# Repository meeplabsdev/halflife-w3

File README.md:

# Piano Keys

# What it is
For the third week of [halflife](https://halflife.hackclub.com/), I decided to create a midi instrument. It uses capacitive touch to recognise when the keys are pressed, and use 16 zones per key (multiplexed). This means that while each key is single touch itself, it supports full multi touch across all the keys. It also allows us to determine the exact position of the finger on the key by taking readings from each zone and interpolating between them (since the readings differ depending on how close or far you are from each zone). It ALSO allows us to determine the velocity the key was pressed with and also the aftertouch pressure being applied, which can be approximated by the rate of change of the distance proxy, and by the reading produced by each zone respectively. (If four zones, one on each size of the finger, all show a lower reading then the finger is not compressed against the key, and if they show a higher reading it is because the finger is pushed harder against the key and has spread out).

# Schematic

# PCB (4 layers)

# Cost
This is a rough outline of the cost, see [`BOM.csv`](BOM.csv) for more details.

| Part | Cost |
| --- | --- |
| [Unpopulated PCB](https://jlcpcb.com/) | $62.10 |
| [Pi Pico](https://thepihut.com/products/raspberry-pi-pico?variant=41925332533443) | $5.08 |
| [Multiplexers](https://www.lcsc.com/product-detail/C6525.html) | $15.11 |
| **Total + Shipping** | **$99.56** |

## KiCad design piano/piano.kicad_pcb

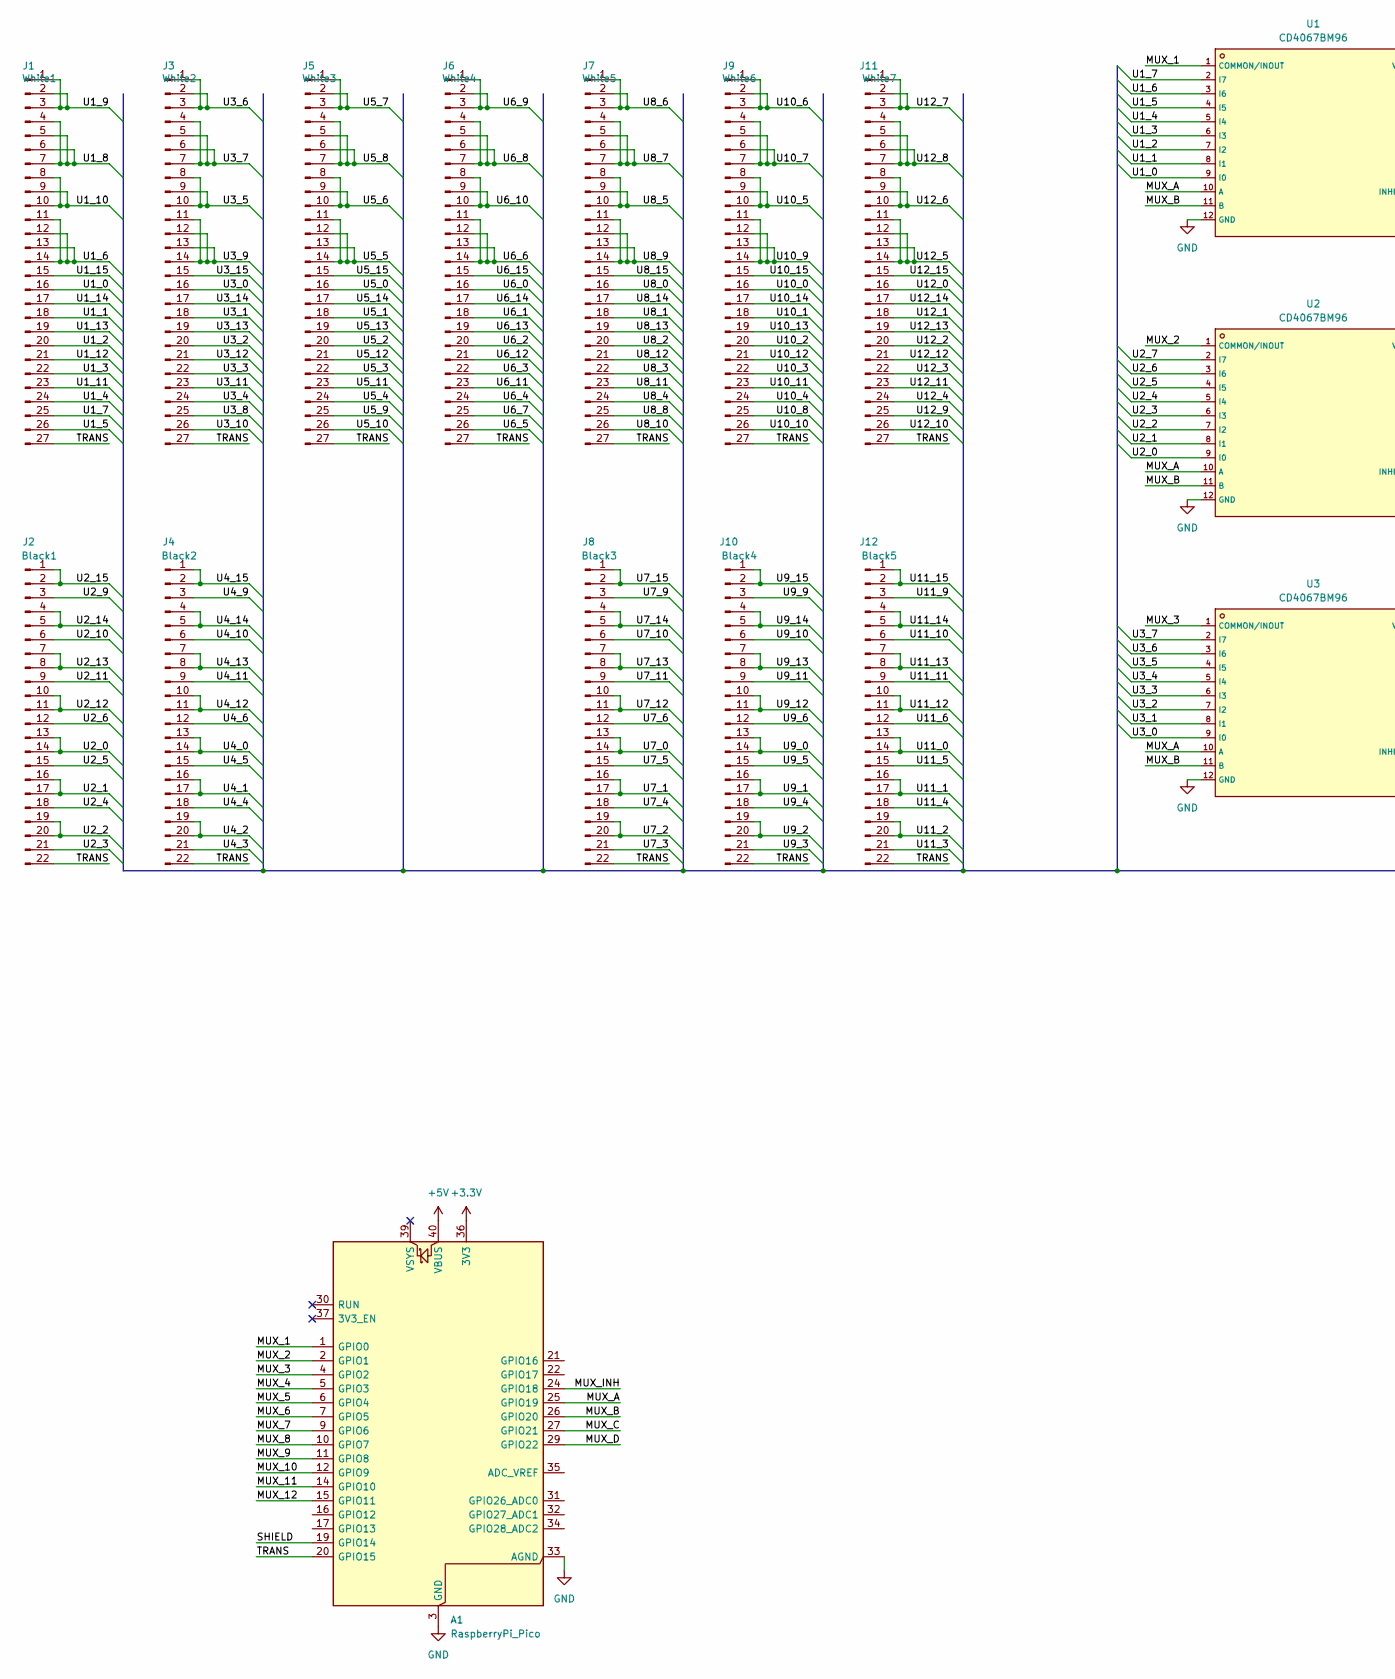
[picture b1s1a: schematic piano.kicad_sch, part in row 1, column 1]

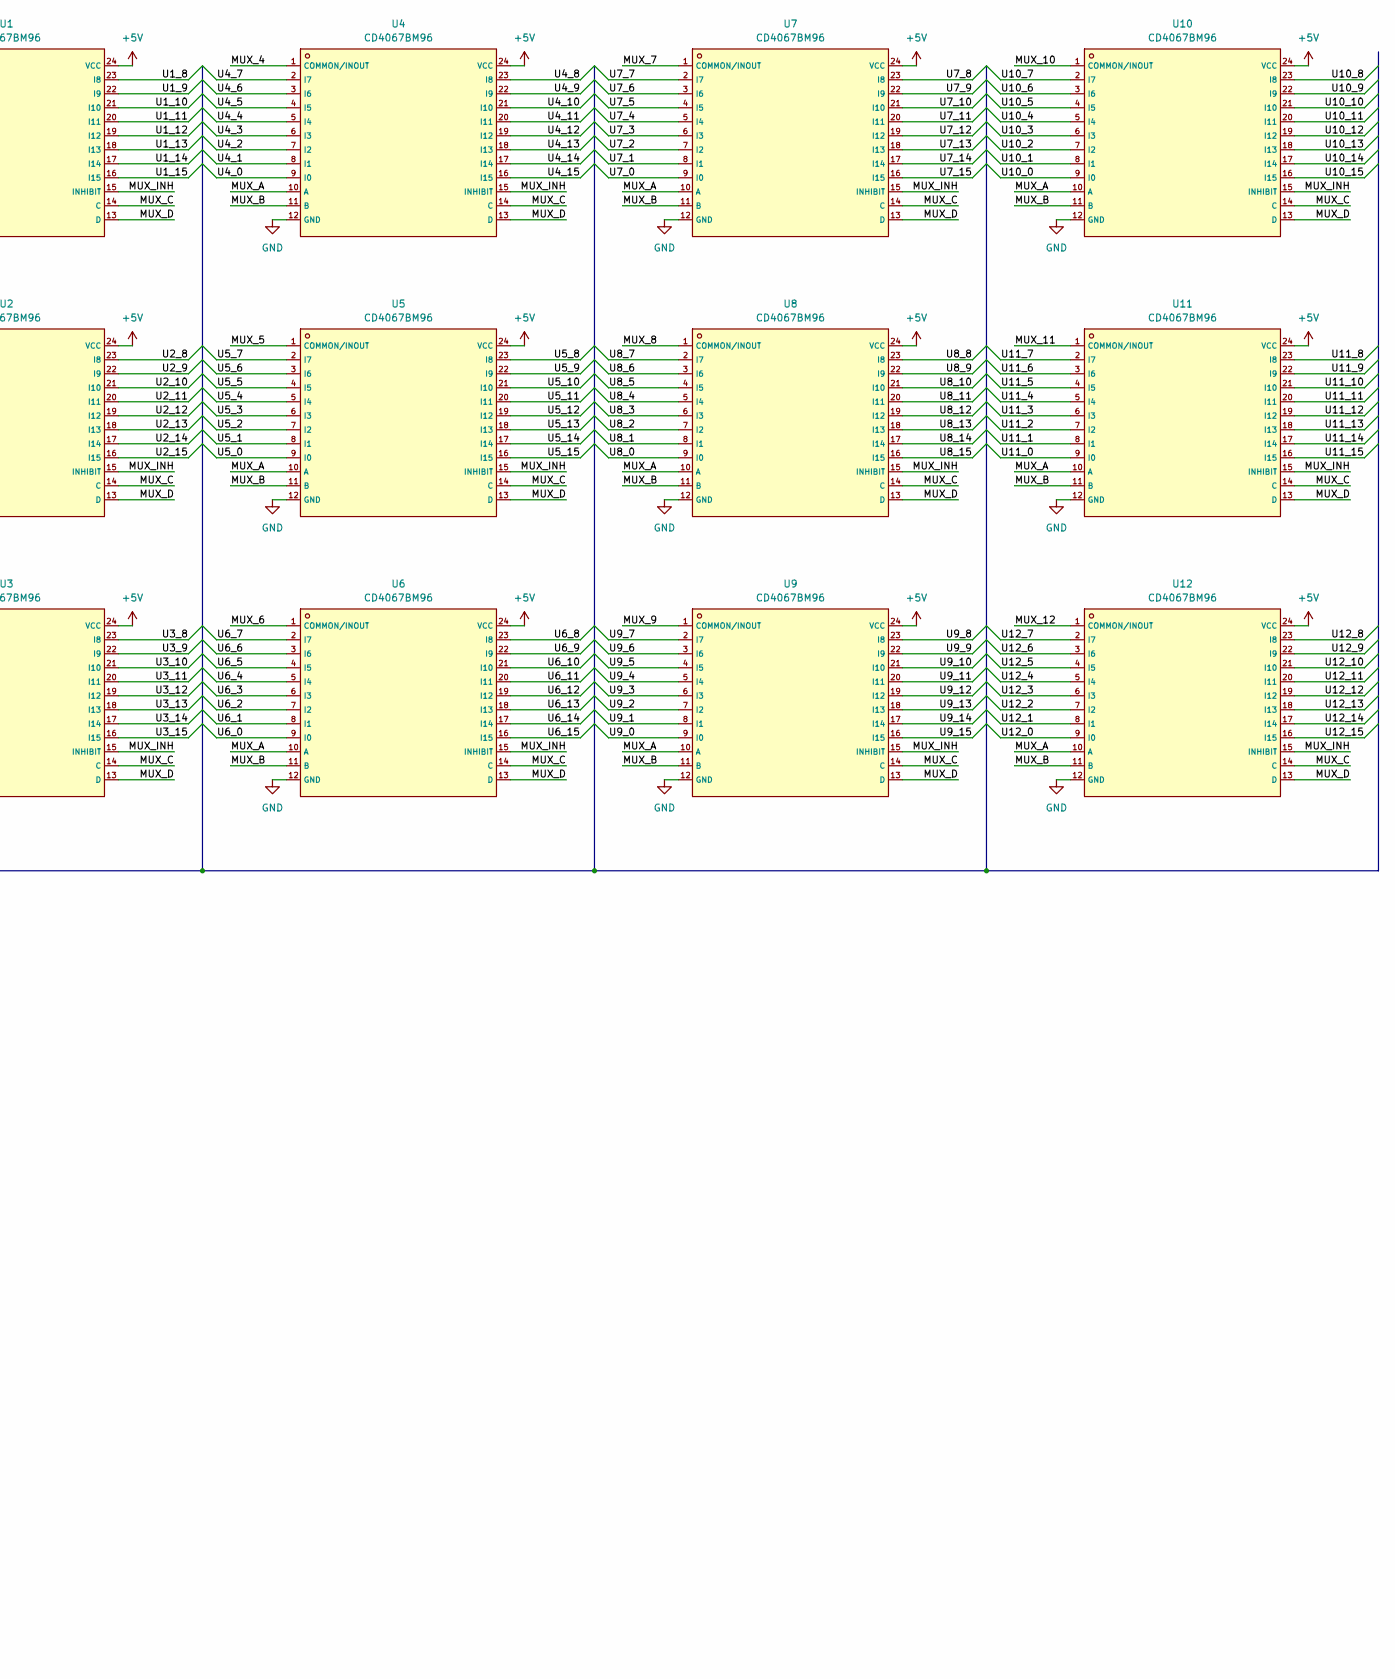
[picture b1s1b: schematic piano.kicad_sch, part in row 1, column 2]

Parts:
A1: RaspberryPi_Pico; RaspberryPi_Pico_Common_SMD
J1: White1; LeftKey
J2: Black1; BlackKey
J3: White2; MiddleKey
J4: Black2; BlackKey
J5: White3; RightKey
J6: White4; LeftKey
J7: White5; MiddleKey
J8: Black3; BlackKey
J9: White6; MiddleKey
J10: Black4; BlackKey
J11: White7; RightKey
J12: Black5; BlackKey
U1, U2, U3, U4, U5, U6, U7, U8, U9, U10, U11, U12: CD4067BM96; C6525_SOIC-24_L15_4-W7_5-P1_27-LS10_3-BL; LCSC C6525

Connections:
+3.3V: A1.36 (3V3)
+5V: A1.40 (VBUS), U1.24 (VCC), U2.24 (VCC), U3.24 (VCC), U4.24 (VCC), U5.24 (VCC), U6.24 (VCC), U7.24 (VCC), U8.24 (VCC), U9.24 (VCC), U10.24 (VCC), U11.24 (VCC), U12.24 (VCC)
/MUX_1: A1.1 (GPIO0), U1.1 (COMMON/INOUT)
/MUX_2: A1.2 (GPIO1), U2.1 (COMMON/INOUT)
/MUX_3: A1.4 (GPIO2), U3.1 (COMMON/INOUT)
/MUX_4: A1.5 (GPIO3), U4.1 (COMMON/INOUT)
/MUX_5: A1.6 (GPIO4), U5.1 (COMMON/INOUT)
/MUX_6: A1.7 (GPIO5), U6.1 (COMMON/INOUT)
/MUX_7: A1.9 (GPIO6), U7.1 (COMMON/INOUT)
/MUX_8: A1.10 (GPIO7), U8.1 (COMMON/INOUT)
/MUX_9: A1.11 (GPIO8), U9.1 (COMMON/INOUT)
/MUX_10: A1.12 (GPIO9), U10.1 (COMMON/INOUT)
/MUX_11: A1.14 (GPIO10), U11.1 (COMMON/INOUT)
/MUX_12: A1.15 (GPIO11), U12.1 (COMMON/INOUT)
/MUX_A: A1.25 (GPIO19), U1.10 (A), U2.10 (A), U3.10 (A), U4.10 (A), U5.10 (A), U6.10 (A), U7.10 (A), U8.10 (A), U9.10 (A), U10.10 (A), U11.10 (A), U12.10 (A)
/MUX_B: A1.26 (GPIO20), U1.11 (B), U2.11 (B), U3.11 (B), U4.11 (B), U5.11 (B), U6.11 (B), U7.11 (B), U8.11 (B), U9.11 (B), U10.11 (B), U11.11 (B), U12.11 (B)
/MUX_C: A1.27 (GPIO21), U1.14 (C), U2.14 (C), U3.14 (C), U4.14 (C), U5.14 (C), U6.14 (C), U7.14 (C), U8.14 (C), U9.14 (C), U10.14 (C), U11.14 (C), U12.14 (C)
/MUX_D: A1.29 (GPIO22), U1.13 (D), U2.13 (D), U3.13 (D), U4.13 (D), U5.13 (D), U6.13 (D), U7.13 (D), U8.13 (D), U9.13 (D), U10.13 (D), U11.13 (D), U12.13 (D)
/MUX_INH: A1.24 (GPIO18), U1.15 (INHIBIT), U2.15 (INHIBIT), U3.15 (INHIBIT), U4.15 (INHIBIT), U5.15 (INHIBIT), U6.15 (INHIBIT), U7.15 (INHIBIT), U8.15 (INHIBIT), U9.15 (INHIBIT), U10.15 (INHIBIT), U11.15 (INHIBIT), U12.15 (INHIBIT)
/SHIELD: A1.19 (GPIO14)
/TRANS: A1.20 (GPIO15), J1.27, J2.22, J3.27, J4.22, J5.27, J6.27, J7.27, J8.22, J9.27, J10.22, J11.27, J12.22
/U1_0: J1.16, U1.9 (I0)
/U1_1: J1.18, U1.8 (I1)
/U1_2: J1.20, U1.7 (I2)
/U1_3: J1.22, U1.6 (I3)
/U1_4: J1.24, U1.5 (I4)
/U1_5: J1.26, U1.4 (I5)
/U1_6: J1.11, J1.12, J1.13, J1.14, U1.3 (I6)
/U1_7: J1.25, U1.2 (I7)
/U1_8: J1.4, J1.5, J1.6, J1.7, U1.23 (I8)
/U1_9: J1.1, J1.2, J1.3, U1.22 (I9)
/U1_10: J1.8, J1.9, J1.10, U1.21 (I10)
/U1_11: J1.23, U1.20 (I11)
/U1_12: J1.21, U1.19 (I12)
/U1_13: J1.19, U1.18 (I13)
/U1_14: J1.17, U1.17 (I14)
/U1_15: J1.15, U1.16 (I15)
/U2_0: J2.13, J2.14, U2.9 (I0)
/U2_1: J2.16, J2.17, U2.8 (I1)
/U2_2: J2.19, J2.20, U2.7 (I2)
/U2_3: J2.21, U2.6 (I3)
/U2_4: J2.18, U2.5 (I4)
/U2_5: J2.15, U2.4 (I5)
/U2_6: J2.12, U2.3 (I6)
/U2_7: U2.2 (I7)
/U2_8: U2.23 (I8)
/U2_9: J2.3, U2.22 (I9)
/U2_10: J2.6, U2.21 (I10)
/U2_11: J2.9, U2.20 (I11)
/U2_12: J2.10, J2.11, U2.19 (I12)
/U2_13: J2.7, J2.8, U2.18 (I13)
/U2_14: J2.4, J2.5, U2.17 (I14)
/U2_15: J2.1, J2.2, U2.16 (I15)
/U3_0: J3.16, U3.9 (I0)
/U3_1: J3.18, U3.8 (I1)
/U3_2: J3.20, U3.7 (I2)
/U3_3: J3.22, U3.6 (I3)
/U3_4: J3.24, U3.5 (I4)
/U3_5: J3.8, J3.9, J3.10, U3.4 (I5)
/U3_6: J3.1, J3.2, J3.3, U3.3 (I6)
/U3_7: J3.4, J3.5, J3.6, J3.7, U3.2 (I7)
/U3_8: J3.25, U3.23 (I8)
/U3_9: J3.11, J3.12, J3.13, J3.14, U3.22 (I9)
/U3_10: J3.26, U3.21 (I10)
/U3_11: J3.23, U3.20 (I11)
/U3_12: J3.21, U3.19 (I12)
/U3_13: J3.19, U3.18 (I13)
/U3_14: J3.17, U3.17 (I14)
/U3_15: J3.15, U3.16 (I15)
/U4_0: J4.13, J4.14, U4.9 (I0)
/U4_1: J4.16, J4.17, U4.8 (I1)
/U4_2: J4.19, J4.20, U4.7 (I2)
/U4_3: J4.21, U4.6 (I3)
/U4_4: J4.18, U4.5 (I4)
/U4_5: J4.15, U4.4 (I5)
/U4_6: J4.12, U4.3 (I6)
/U4_7: U4.2 (I7)
/U4_8: U4.23 (I8)
/U4_9: J4.3, U4.22 (I9)
/U4_10: J4.6, U4.21 (I10)
/U4_11: J4.9, U4.20 (I11)
/U4_12: J4.10, J4.11, U4.19 (I12)
/U4_13: J4.7, J4.8, U4.18 (I13)
/U4_14: J4.4, J4.5, U4.17 (I14)
/U4_15: J4.1, J4.2, U4.16 (I15)
/U5_0: J5.16, U5.9 (I0)
/U5_1: J5.18, U5.8 (I1)
/U5_2: J5.20, U5.7 (I2)
/U5_3: J5.22, U5.6 (I3)
/U5_4: J5.24, U5.5 (I4)
/U5_5: J5.11, J5.12, J5.13, J5.14, U5.4 (I5)
/U5_6: J5.8, J5.9, J5.10, U5.3 (I6)
/U5_7: J5.1, J5.2, J5.3, U5.2 (I7)
/U5_8: J5.4, J5.5, J5.6, J5.7, U5.23 (I8)
/U5_9: J5.25, U5.22 (I9)
/U5_10: J5.26, U5.21 (I10)
/U5_11: J5.23, U5.20 (I11)
/U5_12: J5.21, U5.19 (I12)
/U5_13: J5.19, U5.18 (I13)
/U5_14: J5.17, U5.17 (I14)
/U5_15: J5.15, U5.16 (I15)
/U6_0: J6.16, U6.9 (I0)
/U6_1: J6.18, U6.8 (I1)
/U6_2: J6.20, U6.7 (I2)
/U6_3: J6.22, U6.6 (I3)
/U6_4: J6.24, U6.5 (I4)
/U6_5: J6.26, U6.4 (I5)
/U6_6: J6.11, J6.12, J6.13, J6.14, U6.3 (I6)
/U6_7: J6.25, U6.2 (I7)
/U6_8: J6.4, J6.5, J6.6, J6.7, U6.23 (I8)
/U6_9: J6.1, J6.2, J6.3, U6.22 (I9)
/U6_10: J6.8, J6.9, J6.10, U6.21 (I10)
/U6_11: J6.23, U6.20 (I11)
/U6_12: J6.21, U6.19 (I12)
/U6_13: J6.19, U6.18 (I13)
/U6_14: J6.17, U6.17 (I14)
/U6_15: J6.15, U6.16 (I15)
/U7_0: J8.13, J8.14, U7.9 (I0)
/U7_1: J8.16, J8.17, U7.8 (I1)
/U7_2: J8.19, J8.20, U7.7 (I2)
/U7_3: J8.21, U7.6 (I3)
/U7_4: J8.18, U7.5 (I4)
/U7_5: J8.15, U7.4 (I5)
/U7_6: J8.12, U7.3 (I6)
/U7_7: U7.2 (I7)
/U7_8: U7.23 (I8)
/U7_9: J8.3, U7.22 (I9)
/U7_10: J8.6, U7.21 (I10)
/U7_11: J8.9, U7.20 (I11)
/U7_12: J8.10, J8.11, U7.19 (I12)
/U7_13: J8.7, J8.8, U7.18 (I13)
/U7_14: J8.4, J8.5, U7.17 (I14)
/U7_15: J8.1, J8.2, U7.16 (I15)
/U8_0: J7.16, U8.9 (I0)
/U8_1: J7.18, U8.8 (I1)
/U8_2: J7.20, U8.7 (I2)
/U8_3: J7.22, U8.6 (I3)
/U8_4: J7.24, U8.5 (I4)
/U8_5: J7.8, J7.9, J7.10, U8.4 (I5)
/U8_6: J7.1, J7.2, J7.3, U8.3 (I6)
/U8_7: J7.4, J7.5, J7.6, J7.7, U8.2 (I7)
/U8_8: J7.25, U8.23 (I8)
/U8_9: J7.11, J7.12, J7.13, J7.14, U8.22 (I9)
/U8_10: J7.26, U8.21 (I10)
/U8_11: J7.23, U8.20 (I11)
/U8_12: J7.21, U8.19 (I12)
/U8_13: J7.19, U8.18 (I13)
/U8_14: J7.17, U8.17 (I14)
/U8_15: J7.15, U8.16 (I15)
/U9_0: J10.13, J10.14, U9.9 (I0)
/U9_1: J10.16, J10.17, U9.8 (I1)
/U9_2: J10.19, J10.20, U9.7 (I2)
/U9_3: J10.21, U9.6 (I3)
/U9_4: J10.18, U9.5 (I4)
/U9_5: J10.15, U9.4 (I5)
/U9_6: J10.12, U9.3 (I6)
/U9_7: U9.2 (I7)
/U9_8: U9.23 (I8)
/U9_9: J10.3, U9.22 (I9)
/U9_10: J10.6, U9.21 (I10)
/U9_11: J10.9, U9.20 (I11)
/U9_12: J10.10, J10.11, U9.19 (I12)
/U9_13: J10.7, J10.8, U9.18 (I13)
/U9_14: J10.4, J10.5, U9.17 (I14)
/U9_15: J10.1, J10.2, U9.16 (I15)
/U10_0: J9.16, U10.9 (I0)
/U10_1: J9.18, U10.8 (I1)
/U10_2: J9.20, U10.7 (I2)
/U10_3: J9.22, U10.6 (I3)
/U10_4: J9.24, U10.5 (I4)
/U10_5: J9.8, J9.9, J9.10, U10.4 (I5)
/U10_6: J9.1, J9.2, J9.3, U10.3 (I6)
/U10_7: J9.4, J9.5, J9.6, J9.7, U10.2 (I7)
/U10_8: J9.25, U10.23 (I8)
/U10_9: J9.11, J9.12, J9.13, J9.14, U10.22 (I9)
/U10_10: J9.26, U10.21 (I10)
/U10_11: J9.23, U10.20 (I11)
/U10_12: J9.21, U10.19 (I12)
/U10_13: J9.19, U10.18 (I13)
/U10_14: J9.17, U10.17 (I14)
/U10_15: J9.15, U10.16 (I15)
/U11_0: J12.13, J12.14, U11.9 (I0)
/U11_1: J12.16, J12.17, U11.8 (I1)
/U11_2: J12.19, J12.20, U11.7 (I2)
/U11_3: J12.21, U11.6 (I3)
/U11_4: J12.18, U11.5 (I4)
/U11_5: J12.15, U11.4 (I5)
/U11_6: J12.12, U11.3 (I6)
/U11_7: U11.2 (I7)
/U11_8: U11.23 (I8)
/U11_9: J12.3, U11.22 (I9)
/U11_10: J12.6, U11.21 (I10)
/U11_11: J12.9, U11.20 (I11)
/U11_12: J12.10, J12.11, U11.19 (I12)
/U11_13: J12.7, J12.8, U11.18 (I13)
/U11_14: J12.4, J12.5, U11.17 (I14)
/U11_15: J12.1, J12.2, U11.16 (I15)
/U12_0: J11.16, U12.9 (I0)
/U12_1: J11.18, U12.8 (I1)
/U12_2: J11.20, U12.7 (I2)
/U12_3: J11.22, U12.6 (I3)
/U12_4: J11.24, U12.5 (I4)
/U12_5: J11.11, J11.12, J11.13, J11.14, U12.4 (I5)
/U12_6: J11.8, J11.9, J11.10, U12.3 (I6)
/U12_7: J11.1, J11.2, J11.3, U12.2 (I7)
/U12_8: J11.4, J11.5, J11.6, J11.7, U12.23 (I8)
/U12_9: J11.25, U12.22 (I9)
/U12_10: J11.26, U12.21 (I10)
/U12_11: J11.23, U12.20 (I11)
/U12_12: J11.21, U12.19 (I12)
/U12_13: J11.19, U12.18 (I13)
/U12_14: J11.17, U12.17 (I14)
/U12_15: J11.15, U12.16 (I15)
GND: A1.3 (GND), A1.8 (GND), A1.13 (GND), A1.18 (GND), A1.23 (GND), A1.28 (GND), A1.33 (AGND), A1.38 (GND), U1.12 (GND), U2.12 (GND), U3.12 (GND), U4.12 (GND), U5.12 (GND), U6.12 (GND), U7.12 (GND), U8.12 (GND), U9.12 (GND), U10.12 (GND), U11.12 (GND), U12.12 (GND)

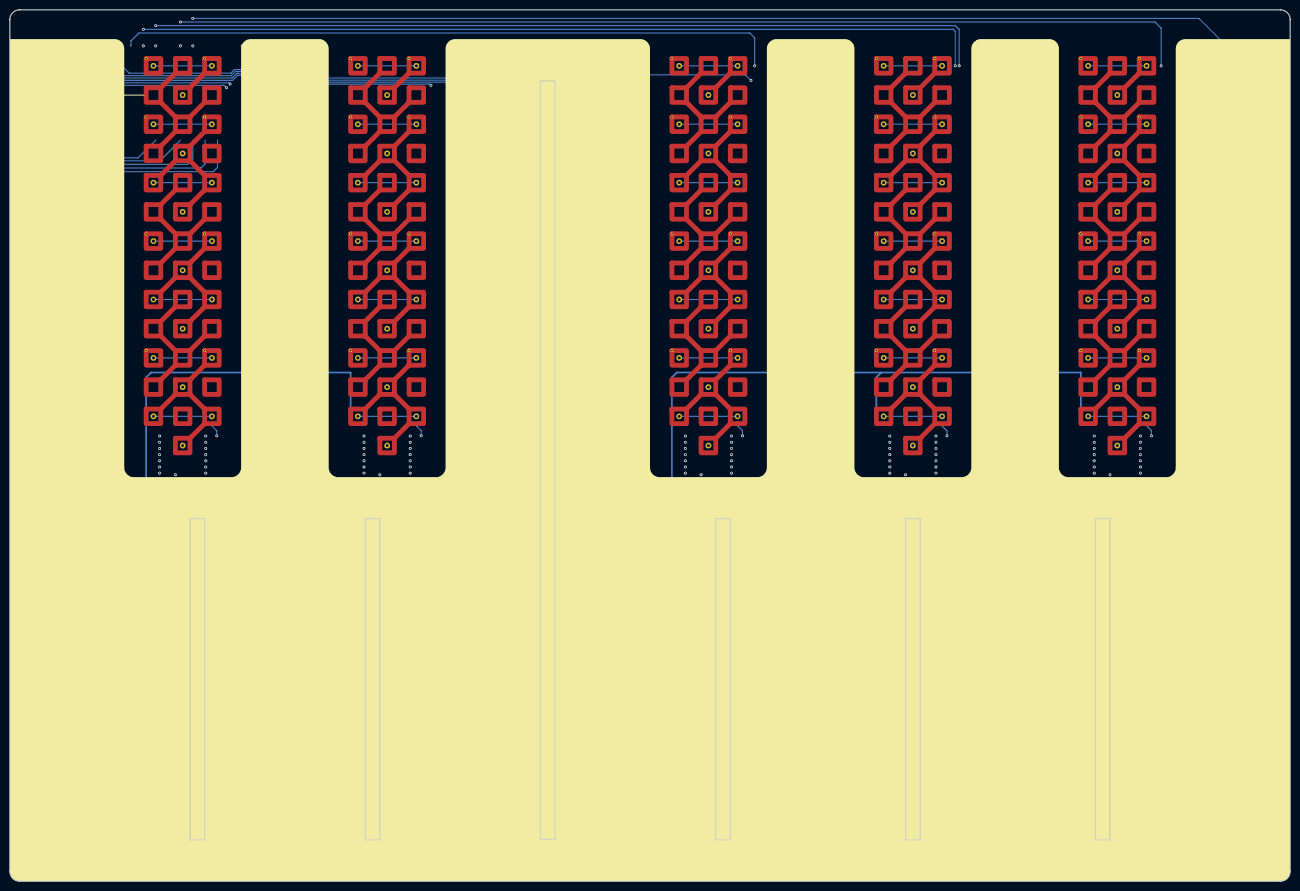
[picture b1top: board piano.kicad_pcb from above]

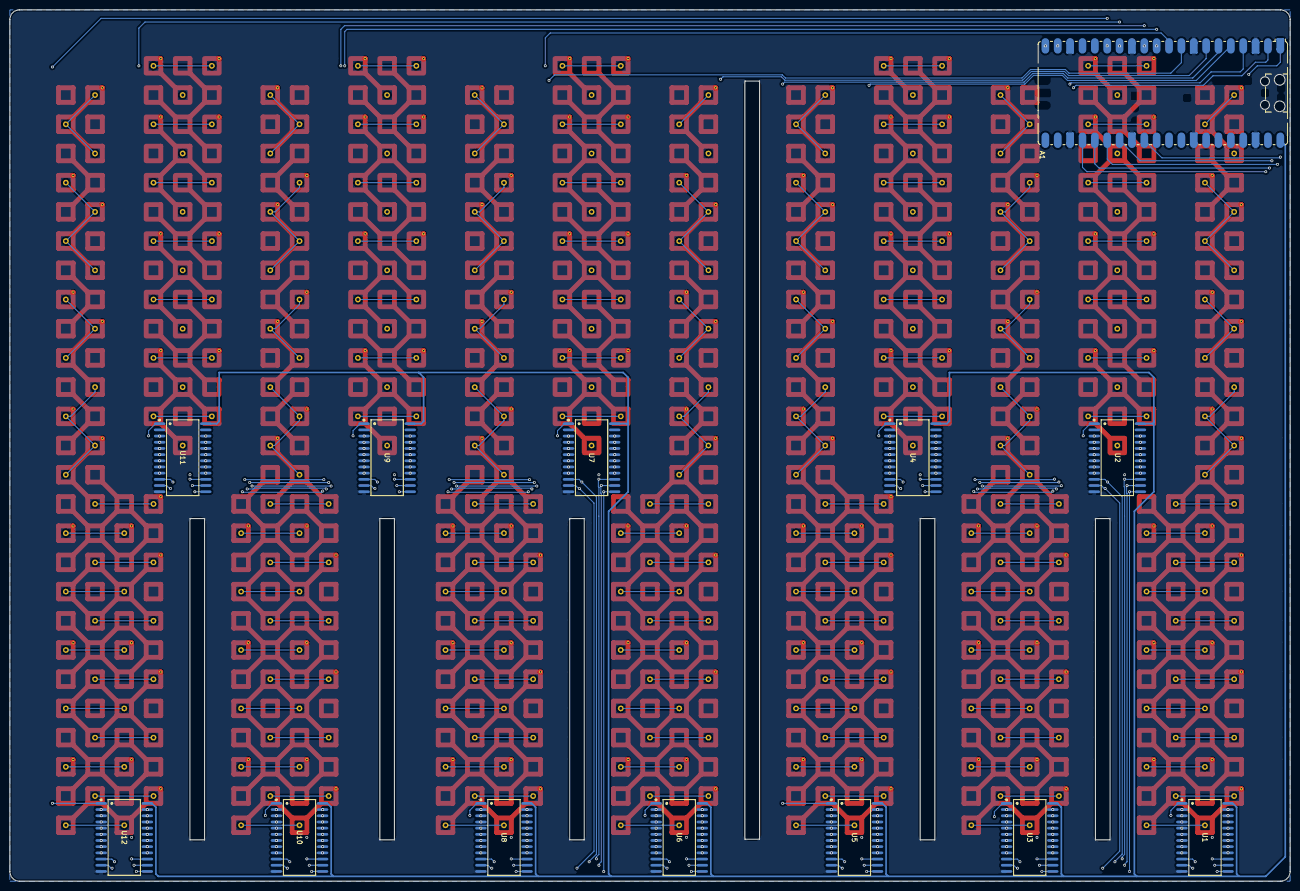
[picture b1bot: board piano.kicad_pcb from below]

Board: 4 copper layers, 263.0 x 179.0 mm, 25 parts (13 on the bottom side), 202 nets.
